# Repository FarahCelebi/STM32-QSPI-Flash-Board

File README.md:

# STM32-QSPI-Flash-Board

A high-speed QSPI interface board: an STM32F407VG reading and writing an
external W25Q128JVS NOR flash chip over a full 4-bit Quad-SPI bus, on a
4-layer, controlled-impedance, length-matched design.

## Schematic

## PCB Layout

## Overview

This board pairs the STM32F407's QUADSPI peripheral (Bank1) with a 16MB
Winbond flash chip, intended as fast external storage for applications like
data logging or firmware staging — workloads where a single-bit SPI EEPROM
would be too slow.

## Design notes

**Power architecture:** 6×VDD pins each get individual 100nF decoupling.
VDDA is isolated from the main 3.3V rail through a ferrite bead and given its
own decoupling, since any digital switching noise on the shared rail can
corrupt ADC readings. VREF+ shares the filtered VDDA rail per the datasheet's
guidance. The two VCAP pins (required by the chip's internal core regulator)
each get a dedicated 2.2µF capacitor — this is mandatory, not optional, for
the chip to start up reliably.

**QUADSPI bus:** CLK, NCS, and IO0-IO3 connect the STM32 to the flash chip
using ST's documented Bank1 pin mapping (PB2, PB6, PD11, PD12, PD13, PE2).
All six signals are routed at 0.2mm width on F.Cu, directly over the
dedicated In1.Cu ground plane, to maintain a consistent ~50Ω single-ended
impedance.

**Length matching:** the STM32's QUADSPI pins are split across two different
edges of the 100-pin package — CLK/NCS exit from one side, the four data
lines from another. This made equal-length routing significantly harder than
a single-edge bus would be, and pushed the design through several rounds of
placement adjustment and deliberate trace lengthening (using gentle,
wide-radius meanders rather than tight serpentines, to avoid introducing
reflections on the clock line) before reaching the final result below.

| Iteration | Spread (longest − shortest) | Approx. skew |
|---|---|---|
| Initial placement | ~38mm | ~228ps |
| After 3 rounds of placement adjustment | ~17.2mm | ~103ps |
| After targeted length tuning | ~9.9mm | ~60ps |
| Final | **~3.0mm** | **~18ps** |

The final 3mm spread corresponds to roughly 18ps of skew, comfortably within
the general guideline threshold (~60ps) for reliable 80MHz QUADSPI
operation, with substantial margin to spare. If a future revision needs even
more headroom, dropping the target clock to 50MHz would relax this budget
further still.

## Manufacturing

- 4-layer stackup: F.Cu (signal) / In1.Cu (GND plane) / In2.Cu (power plane)
  / B.Cu (routing overflow)
- Passed DRC with 0 violations, 0 unconnected nets
- Gerbers and drill files generated

## Tools

- KiCad

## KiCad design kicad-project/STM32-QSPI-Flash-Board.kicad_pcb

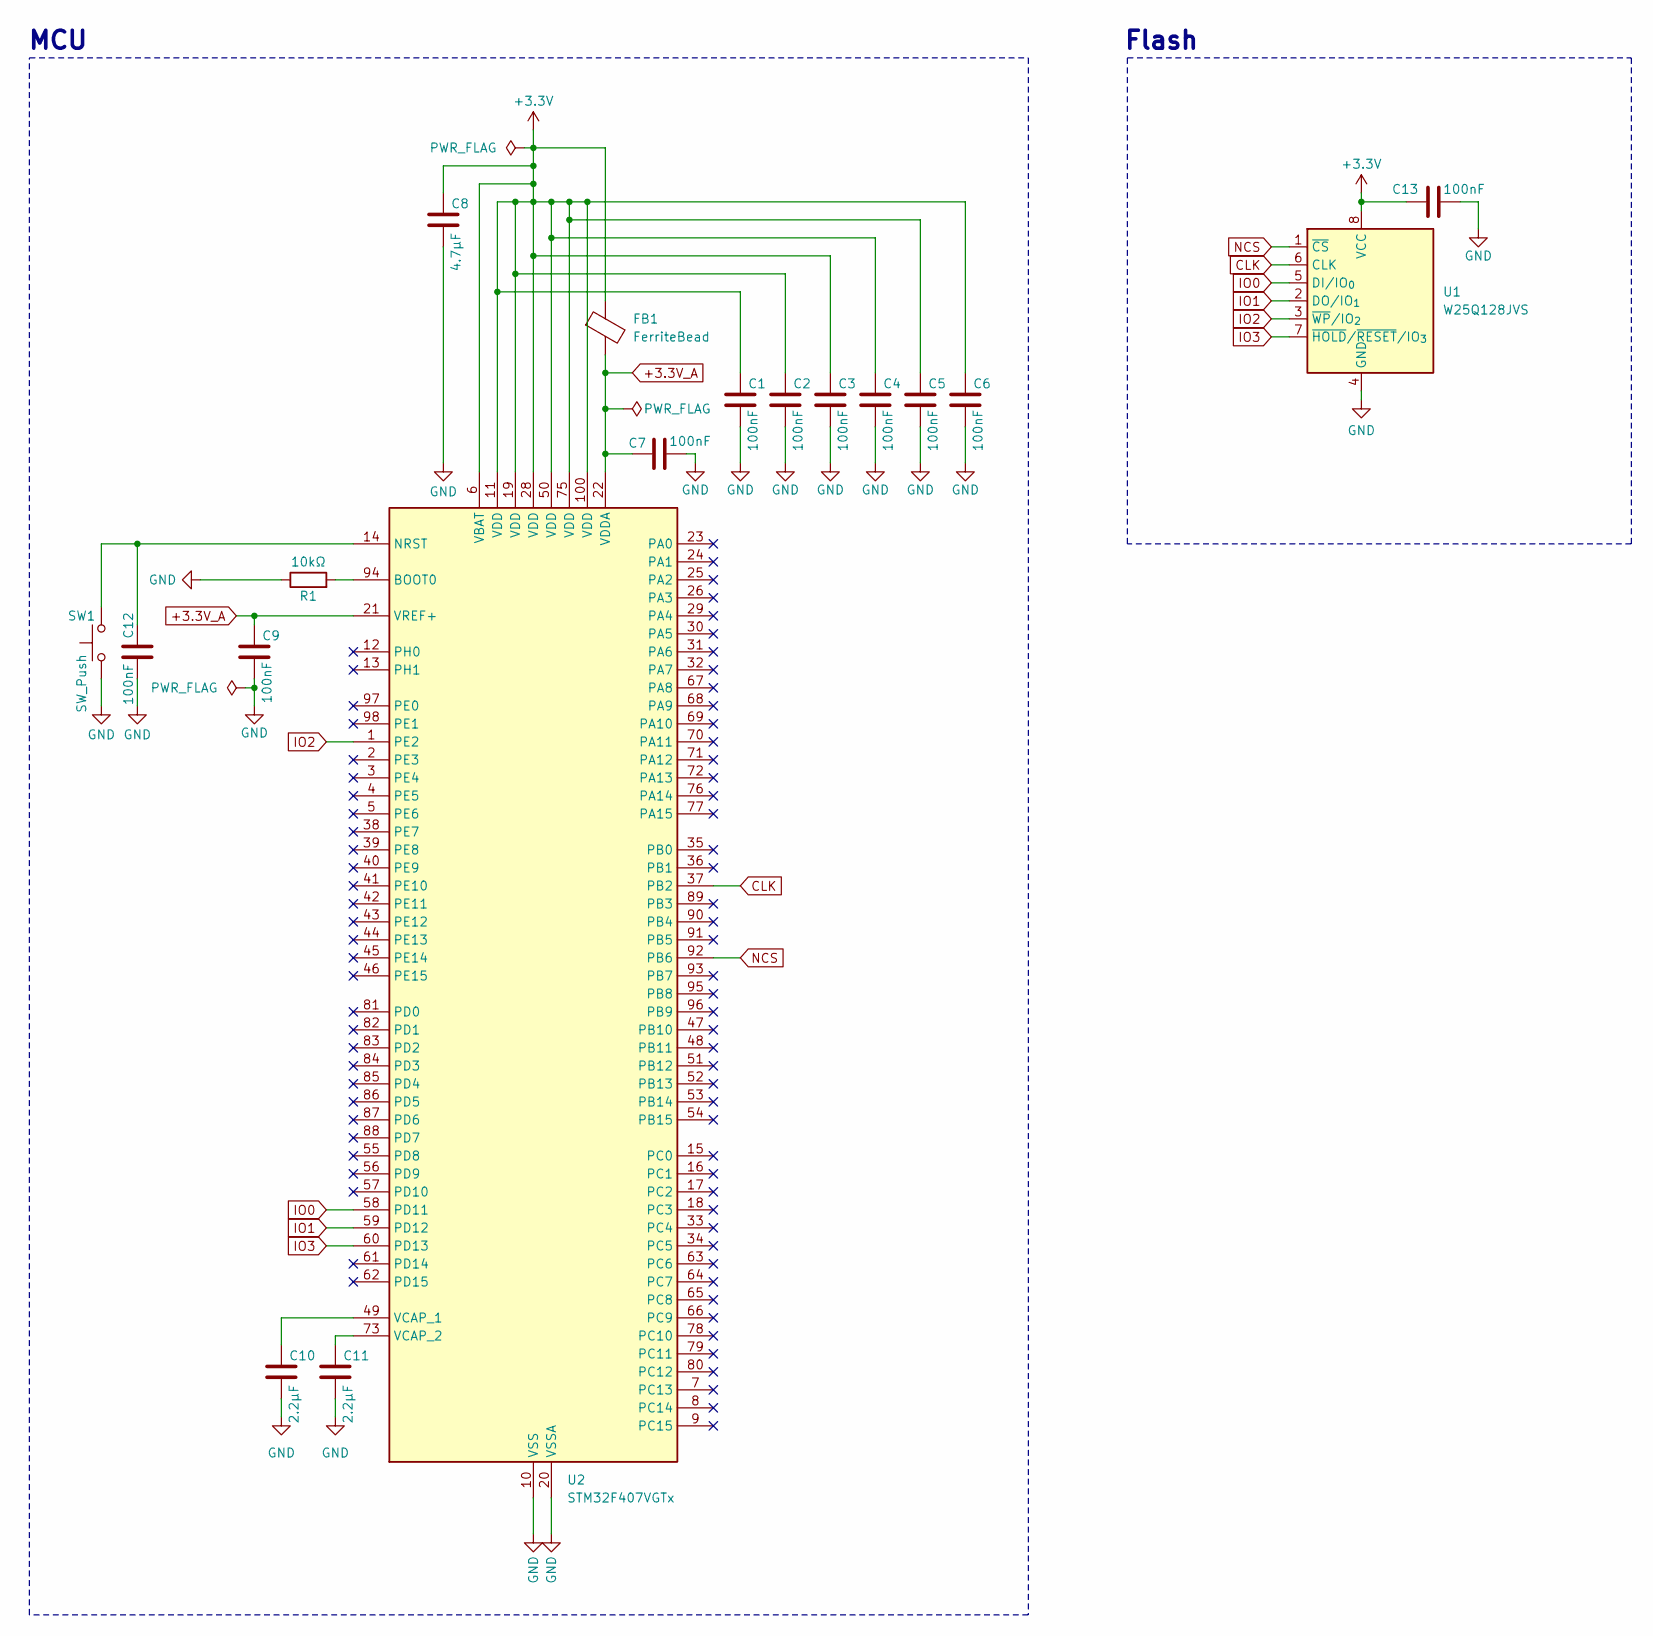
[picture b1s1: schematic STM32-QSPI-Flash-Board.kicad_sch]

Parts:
C1, C2, C3, C4, C5, C6, C7, C9, C12, C13: 100nF
C8: 4.7µF
C10, C11: 2.2µF
FB1: FerriteBead
R1: 10kΩ
SW1: SW_Push
U1: W25Q128JVS; SOIC-8_5.3x5.3mm_P1.27mm
U2: STM32F407VGTx; LQFP-100_14x14mm_P0.5mm

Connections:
+3.3V: C1.1, C2.1, C3.1, C4.1, C5.1, C6.1, C8.1, C13.1, FB1.1, U1.8 (VCC), U2.6 (VBAT), U2.11 (VDD), U2.19 (VDD), U2.28 (VDD), U2.50 (VDD), U2.75 (VDD), U2.100 (VDD)
+3.3V_A: C7.1, C9.1, FB1.2, U2.21 (VREF+), U2.22 (VDDA)
CLK: U1.6 (CLK), U2.37 (PB2)
GND: C1.2, C2.2, C3.2, C4.2, C5.2, C6.2, C7.2, C8.2, C9.2, C10.2, C11.2, C12.2, C13.2, R1.1, SW1.1, U1.4 (GND), U2.10 (VSS), U2.20 (VSSA), U2.27 (VSS), U2.74 (VSS), U2.99 (VSS)
IO0: U1.5 (DI/IO_{0}), U2.58 (PD11)
IO1: U1.2 (DO/IO_{1}), U2.59 (PD12)
IO2: U1.3 (~WP/IO_{2}), U2.1 (PE2)
IO3: U1.7 (~HOLD/~RESET/IO_{3}), U2.60 (PD13)
NCS: U1.1 (~CS), U2.92 (PB6)
unnamed: R1.2, U2.94 (BOOT0)
unnamed: C12.1, SW1.2, U2.14 (NRST)
unnamed: C10.1, U2.49 (VCAP_1)
unnamed: C11.1, U2.73 (VCAP_2)

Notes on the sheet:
MCU
Flash

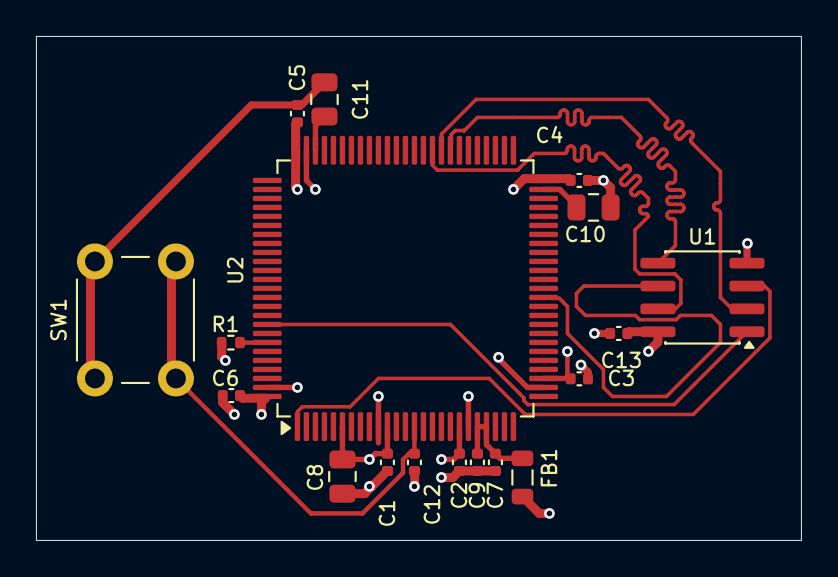
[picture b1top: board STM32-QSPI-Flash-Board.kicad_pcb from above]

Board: 4 copper layers, 42.5 x 28.0 mm, 18 parts (0 on the bottom side), 13 nets.

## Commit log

2026-06-26 Complete schematic: STM32F407 power architecture and QUADSPI flash interface
    Power section covers VDD, VDDA (ferrite-isolated), VCAP regulator caps, and NRST. QUADSPI bus (CLK, NCS, IO0-IO3) wired to a W25Q128JVS flash chip using ST's confirmed Bank1 pin mapping (PB2/PB6/PD11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
2026-06-26 Complete schematic: power architecture and QUADSPI flash interface
2026-06-29 Complete board: 4-layer QUADSPI design, DRC clean, Gerbers generated
